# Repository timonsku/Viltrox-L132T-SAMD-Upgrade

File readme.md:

Replacment PCB for Viltrox L132T MCU
------------------------------------

This tries to replace the MCU on Viltrox L132T photo light with a SAMD21.
Apart from this "graft" you also need to replace the LDO present on the board with a 3v3 one.
F.e. AP2205-33YR-13 https://www.mouser.de/ProductDetail/621-AP2205-33YR-13

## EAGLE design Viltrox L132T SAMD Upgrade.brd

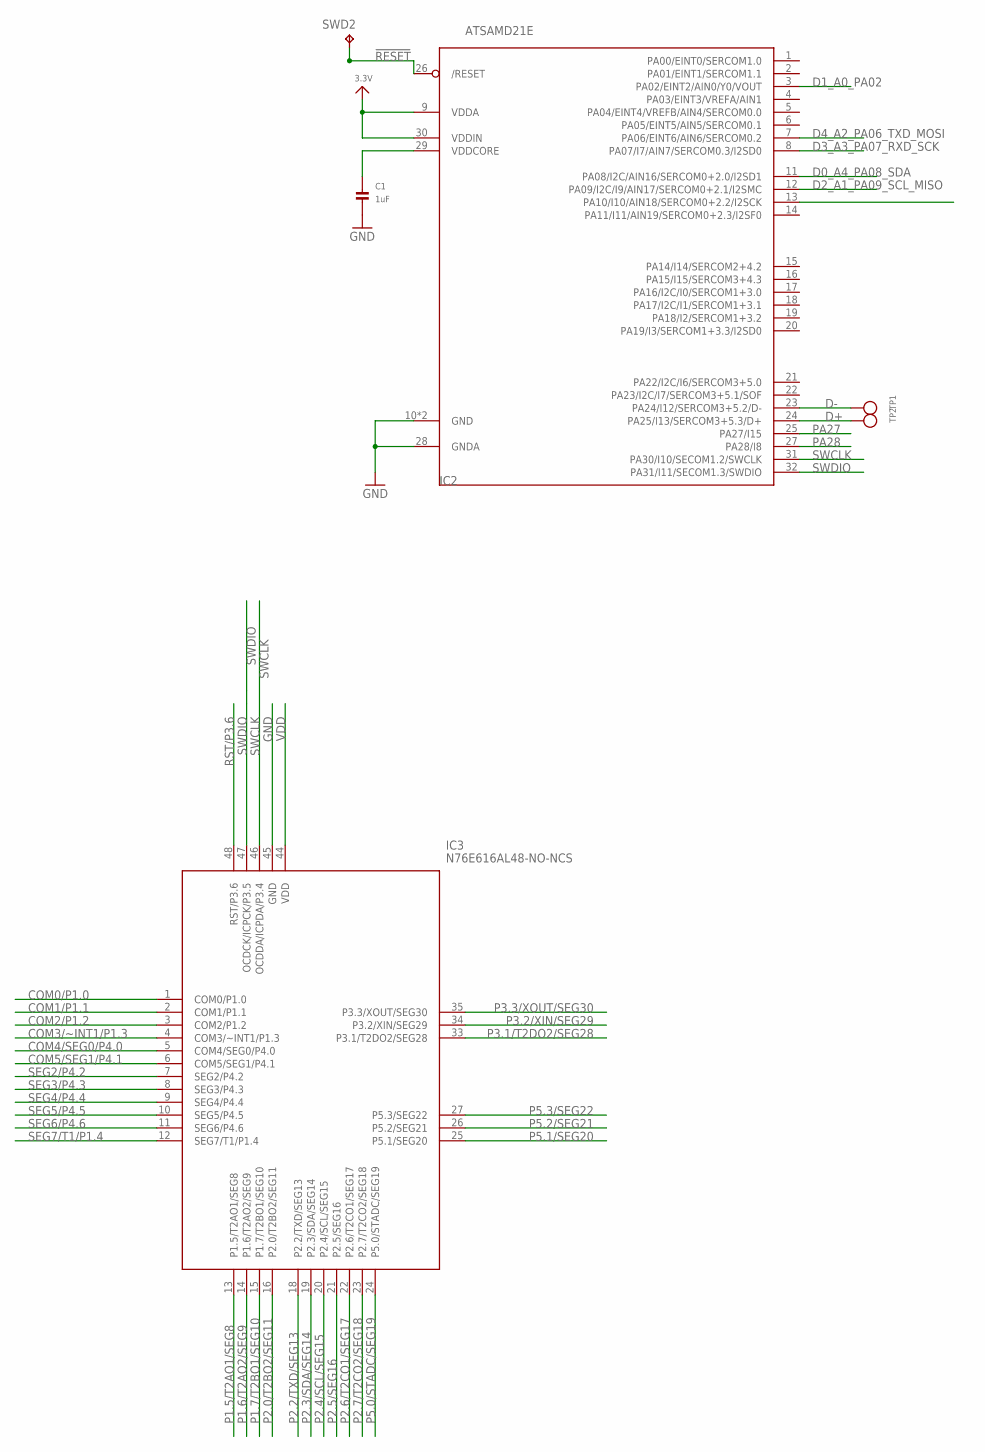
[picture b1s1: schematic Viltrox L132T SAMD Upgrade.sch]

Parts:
C1: 1uF; _0402MP
IC2: ATSAMD21E; QFN32_5MM
IC3: N76E616AL48-NO-NCS; N76-NO-NC-QFP50P900X900X160-48N
SWD2: TPB1,27; B1,27
TP1, TP2: TESTPOINTROUND2MM; TESTPOINT_ROUND_2MM

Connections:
3.3V: IC2.9 (VDDA), IC2.30 (VDDIN)
!RESET: IC2.26 (/RESET), SWD2.TP
COM0/P1.0: IC3.1 (COM0/P1.0)
COM1/P1.1: IC3.2 (COM1/P1.1)
COM2/P1.2: IC3.3 (COM2/P1.2)
COM3/~INT1/P1.3: IC3.4 (COM3/~INT1/P1.3)
COM4/SEG0/P4.0: IC3.5 (COM4/SEG0/P4.0)
COM5/SEG1/P4.1: IC3.6 (COM5/SEG1/P4.1)
D0_A4_PA08_SDA: IC2.11 (PA08/I2C/AIN16/SERCOM0+2.0/I2SD1)
D1_A0_PA02: IC2.3 (PA02/EINT2/AIN0/Y0/VOUT)
D2_A1_PA09_SCL_MISO: IC2.12 (PA09/I2C/I9/AIN17/SERCOM0+2.1/I2SMC)
D3_A3_PA07_RXD_SCK: IC2.8 (PA07/I7/AIN7/SERCOM0.3/I2SD0)
D4_A2_PA06_TXD_MOSI: IC2.7 (PA06/EINT6/AIN6/SERCOM0.2)
D+: IC2.24 (PA25/I13/SERCOM3+5.3/D+), TP2.P$1
D-: IC2.23 (PA24/I12/SERCOM3+5.2/D-), TP1.P$1
GND: C1.2, IC2.10 (GND), IC2.28 (GNDA), IC2.33 (GND), IC3.45 (GND)
P1.5/T2AO1/SEG8: IC3.13 (P1.5/T2AO1/SEG8)
P1.6/T2AO2/SEG9: IC3.14 (P1.6/T2AO2/SEG9)
P1.7/T2BO1/SEG10: IC3.15 (P1.7/T2BO1/SEG10)
P2.0/T2BO2/SEG11: IC3.16 (P2.0/T2BO2/SEG11)
P2.2/TXD/SEG13: IC3.18 (P2.2/TXD/SEG13)
P2.3/SDA/SEG14: IC3.19 (P2.3/SDA/SEG14)
P2.4/SCL/SEG15: IC3.20 (P2.4/SCL/SEG15)
P2.5/SEG16: IC3.21 (P2.5/SEG16)
P2.6/T2CO1/SEG17: IC3.22 (P2.6/T2CO1/SEG17)
P2.7/T2CO2/SEG18: IC3.23 (P2.7/T2CO2/SEG18)
P3.1/T2DO2/SEG28: IC3.33 (P3.1/T2DO2/SEG28)
P3.2/XIN/SEG29: IC3.34 (P3.2/XIN/SEG29)
P3.3/XOUT/SEG30: IC3.35 (P3.3/XOUT/SEG30)
P5.0/STADC/SEG19: IC3.24 (P5.0/STADC/SEG19)
P5.1/SEG20: IC3.25 (P5.1/SEG20)
P5.2/SEG21: IC3.26 (P5.2/SEG21)
P5.3/SEG22: IC3.27 (P5.3/SEG22)
PA27: IC2.25 (PA27/I15)
PA28: IC2.27 (PA28/I8)
RST/P3.6: IC3.48 (RST/P3.6)
SEG2/P4.2: IC3.7 (SEG2/P4.2)
SEG3/P4.3: IC3.8 (SEG3/P4.3)
SEG4/P4.4: IC3.9 (SEG4/P4.4)
SEG5/P4.5: IC3.10 (SEG5/P4.5)
SEG6/P4.6: IC3.11 (SEG6/P4.6)
SEG7/T1/P1.4: IC3.12 (SEG7/T1/P1.4)
SWCLK: IC2.31 (PA30/I10/SECOM1.2/SWCLK), IC3.46 (OCDDA/ICPDA/P3.4)
SWDIO: IC2.32 (PA31/I11/SECOM1.3/SWDIO), IC3.47 (OCDCK/ICPCK/P3.5)
VDD: IC3.44 (VDD)
VDDCORE1: C1.1, IC2.29 (VDDCORE)

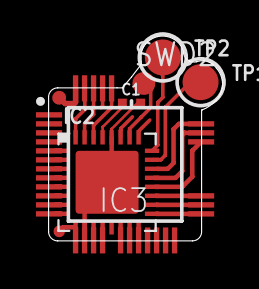
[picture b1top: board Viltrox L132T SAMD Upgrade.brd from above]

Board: 2 copper layers, 9.7 x 11.4 mm, 6 parts (0 on the bottom side), 8 nets.

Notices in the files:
parts and their libraries:
microbuilder: This work is placed in the public domain, and may be freely used for commercial and non-commercial work with the following conditions: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
